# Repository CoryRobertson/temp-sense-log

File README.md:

# serial-temp-sense-log
This is a rust program that reads the serial port of a raspberry pi pico and parses out the temperature.
There is a raspberry pi circuit-python program as well as a rust program to interpret it. 

The serial solution works wonderful at the moment, I have no issues with using it for over 24 hours straight on my linux server. My next focus is using a pico W to host a web server that has the info on it.

Readme.md currently WIP

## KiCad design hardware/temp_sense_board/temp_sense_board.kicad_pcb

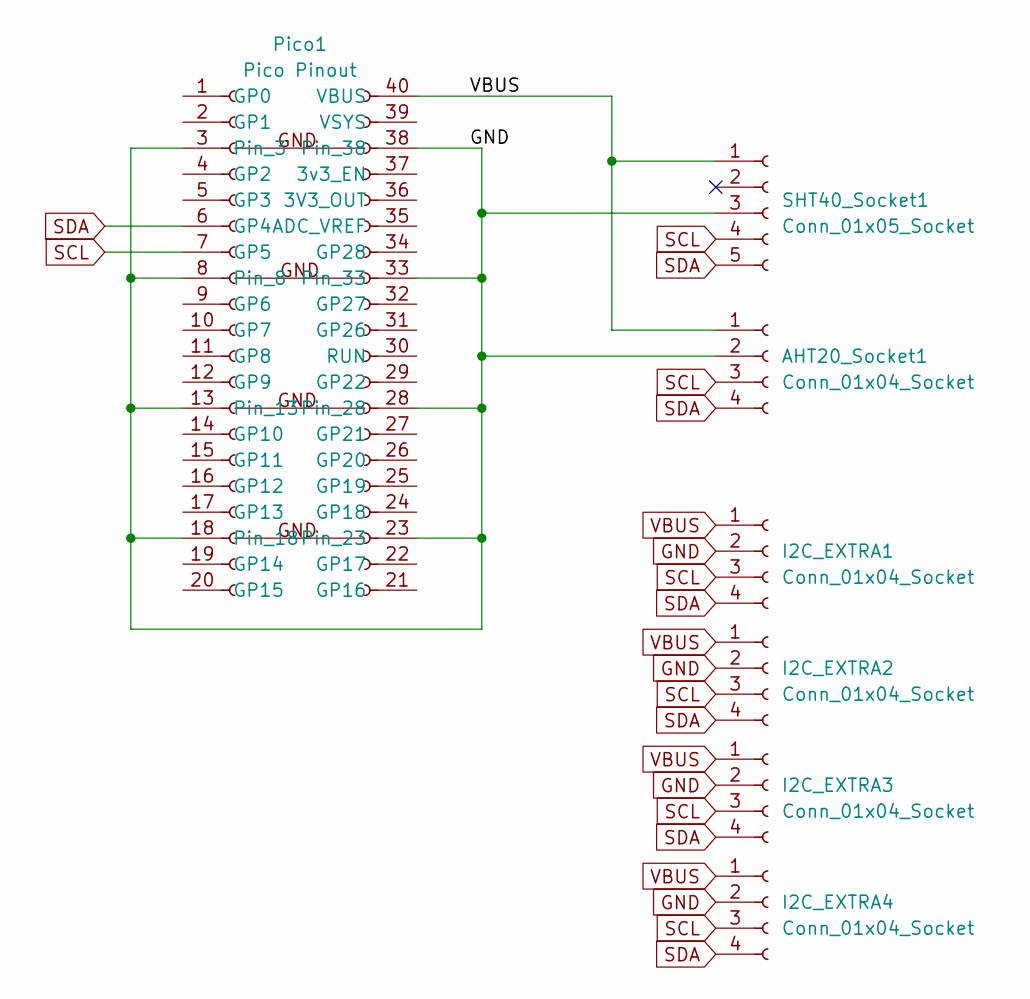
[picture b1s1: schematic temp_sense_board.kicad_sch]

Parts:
AHT20_Socket1: Conn_01x04_Socket; PinSocket_1x04_P2.54mm_Vertical
I2C_EXTRA1, I2C_EXTRA2, I2C_EXTRA3, I2C_EXTRA4: Conn_01x04_Socket; PinSocket_1x04_P2.54mm_Vertical
Pico1: Pico Pinout; PicoSocket
SHT40_Socket1: Conn_01x05_Socket; PinSocket_1x05_P2.54mm_Vertical

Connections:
GND: AHT20_Socket1.2, I2C_EXTRA1.2, I2C_EXTRA2.2, I2C_EXTRA3.2, I2C_EXTRA4.2, Pico1.3, Pico1.8, Pico1.13, Pico1.18, Pico1.23, Pico1.28, Pico1.33, Pico1.38, SHT40_Socket1.3
SCL: AHT20_Socket1.3, I2C_EXTRA1.3, I2C_EXTRA2.3, I2C_EXTRA3.3, I2C_EXTRA4.3, Pico1.7 (GP5), SHT40_Socket1.4
SDA: AHT20_Socket1.4, I2C_EXTRA1.4, I2C_EXTRA2.4, I2C_EXTRA3.4, I2C_EXTRA4.4, Pico1.6 (GP4), SHT40_Socket1.5
VBUS: AHT20_Socket1.1, I2C_EXTRA1.1, I2C_EXTRA2.1, I2C_EXTRA3.1, I2C_EXTRA4.1, Pico1.40 (VBUS), SHT40_Socket1.1

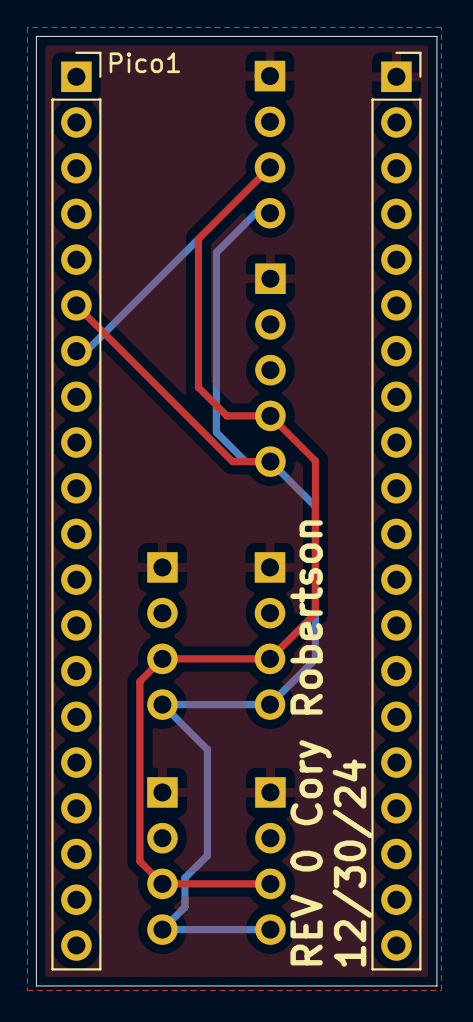
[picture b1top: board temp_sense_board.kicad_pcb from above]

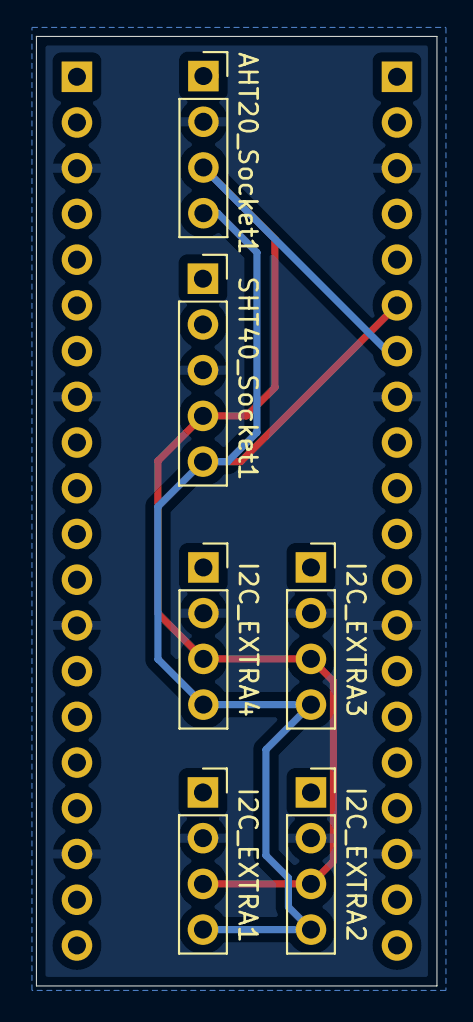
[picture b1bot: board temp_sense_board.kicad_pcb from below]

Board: 2 copper layers, 22.2 x 52.8 mm, 7 parts (6 on the bottom side), 4 nets.

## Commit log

2022-11-24 Initial working commit. basic functionality.
2022-11-24 Logging to file works now.
2022-11-24 Added README.md and code.py for pico device.
2022-11-27 Program now outputs csv format numbers, so it can be imported to a spreadsheet software.
2022-11-27 Program now outputs to a log directory, not just where the program root is.
2022-11-27 Removed comma, so we combine date and time so google sheets reads the data better.
2022-11-28 Device list parsing works, unwraps present at the moment.
2022-11-28 Removed a few unwraps, code now will more likely run smoothly when errors are present.
2022-12-05 Fixed thread joining bug, program now outputs correct file extension for output data.
2024-12-20 new setup who dis
2024-12-20 Successful compile, needs testing, as of now is entirely example code
2024-12-26 changes to firmware and temp server to allow for basic transmission of data
2024-12-27 Added firmware pointers for wireless device, added TODO for parsing floats,
2024-12-29 Code is untested, but it should be closed to where he intended output is
2024-12-30 successfully relays info to web server
2024-12-30 Moved sensor reader and uploader to a task, added TODO
2024-12-30 Used more intelligent way to make generic the way the code reads sensors and executes respective tasks
2024-12-30 Added KiCad project, probably not going to actually fabricate it but I wanted to have something just incase I get any inspiration :)
2024-12-31 Updated PCB and Schematic
2025-01-01 555 timer added, not to board yet
2025-01-03 Termperature server works now!
2025-01-04 Web server can now plot the data, its not intended to be the best way to use the data, but is more intended to be an at a glance easily readable grouping of data
2025-01-14 Updated firmware with lints, added location print in data server
2025-01-14 Implemented DHCP environment variable for static ip address in firmware, also added main home page for web server that displays active temp sensors
2025-01-14 Updated web server to have last modification date appended to main page, as well as MIA sensor listing
2025-01-14 Plot images now are also put in the log folder
2025-01-14 Files are now properly opened on startup using open options, as well as paths are more cleanly used
2025-01-14 Bind port is now an environment variable, lints, fmt
2025-01-16 Added a timeout system reset when web server requests take too long. This is likely going to be needed to be done better, future testing is required.
2025-01-21 prettier
2025-03-02 Updated dependencies when possible, added a uptime limit on pico before a reset
2025-03-05 Removed previously added hard reset timer, as it seems my network is the one causing the issue when ever a disconnection occurs, there is a chance for the device to hang while waiting for DHCP to res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
